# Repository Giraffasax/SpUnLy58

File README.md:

# The SpUnLy58 Keyboard
The SpUnLy58 is **Sp**layed **Un**ibody Li**ly58** layout [6*4 + 4key] keyboard. This is a minimal design keyboard that is wireless first. This design requires a Nice!Nano v2, supports a Nice!View,there are no LEDs, and a case is recommended to protect the up to 750mAh battery.

<p style="text-align: center;">Build of SpUnLy v1.2 <p>

## Notable Features
- Choc V1 support [Hotswap and Soldered]
- "Split" unibody design with 19 deg angle (measured at middle finger column)
- Column Stagger
- Aggressive Pinky splay with Minimal splay for all other columns
- Aggressive Pinky stagger
- Fanned Thumb Cluster
- Nice!Nano v2 **[ REQUIRED ]**
- Nice!View Support
- JST Battery Connector

## SpUnLy58 v1.1 Updates
- Reduced vertical spacing from 18mm -> 17mm
- Increased battery cutout from 36x52mm -> 37x57mm
- Fixed incorrect JST connector footprint
## SpUnLy58 v1.2 Updates
- Removed inner and outer column splay
- Increased pinky stagger
- Reduced thumb key spacing and increased fan angle
- Added Ground fill

### Sponsor:
PCBway sponsored the manufacturing of v1.2 main pcb and the stainless steel bottom plates. If you would like to see more pictures and read my review see them [here.](Reference/PCBWay_Review.md)
___

<p style="text-align: center;">SpUnLy58 v1 PCB<p>

<p style="text-align: center;">SpUnLy58 v1.1 PCB<p>

<p style="text-align: center;">SpUnLy58 v1.2 PCB<p>

___
## Parts List 
| Name | Quantity | Example URL |
|------|----------|-------------|
| SpUnLy58 PCB | 1  | https://github.com/Giraffasax/SpUnLy58/blob/main/KiCad/Gerber/SpUnLy58_Gerber.zip |
| Kailh Choc v1 Switches | 58 | https://typeractive.xyz/products/choc-switches?variant=46024772387047 |
| Kailh Choc v1 Keycaps (Choc Spacing) | 58 | https://fkcaps.com/custom/create/keycaps?option=mbk-pbt-pu&color=black |
| Nice!Nano v2 | 1 | https://typeractive.xyz/products/nice-nano |
| Nice!View or OLED (Optional) | 1 | https://typeractive.xyz/products/nice-view |
| Mill Max Ultra Low Profile Sockets (Optional) | 2 | https://www.littlekeyboards.com/collections/miscellaneous/products/ultra-low-profile-sockets |
| 1N4148W Diodes (SMD or TH) | 58 | https://typeractive.xyz/products/smd-diodes |
| Kailch Choc Hotswap Sockets (Optional) | 58 | https://typeractive.xyz/products/hotswap-sockets?variant=45742200324327 |
| Panasonic EVQPU Reset Switch | 1 | https://typeractive.xyz/products/reset-button |
| Alps miniature SPDT switch | 1 | https://typeractive.xyz/products/power-switch |
| JST PH 2.0mm Battery Jack | 1 | https://typeractive.xyz/products/battery-jack |
| 3.7v 750mAh 403450 Battery | 1 | https://typeractive.xyz/products/lithium-battery-750mah |

Note: I used the ultra low profile Mill Max sockets for both the controller and display to have them sit lower than the switch height to protect them in travel.

## Sandwich Case Part List
| Name | Quantity | Example URL |
|------|----------|-------------|
| Bottom Plate - PCB | 0 or 1 | https://github.com/Giraffasax/SpUnLy58/blob/main/KiCad/Gerber/Bottom_Plate_Gerber.zip |
| Bottom Plate - Metal | 0 or 1 | https://github.com/Giraffasax/SpUnLy58/blob/main/KiCad/SpUnLy58_Bottom.step |
| Top Plate | 1 | https://github.com/Giraffasax/SpUnLy58/blob/main/KiCad/Gerber/Top_Plate_Gerber.zip |
| 6mm M2 Standoffs | 10 | https://splitkb.com/products/brass-m2-spacers?variant=42396969140483 |
| 4mm M2 Screws | 20 | https://splitkb.com/products/m2-screws?_pos=2&_sid=9c9502b8a&_ss=r |

## Firmware
ZMK Firmware: https://github.com/Giraffasax/zmk-SpUnLy58-config

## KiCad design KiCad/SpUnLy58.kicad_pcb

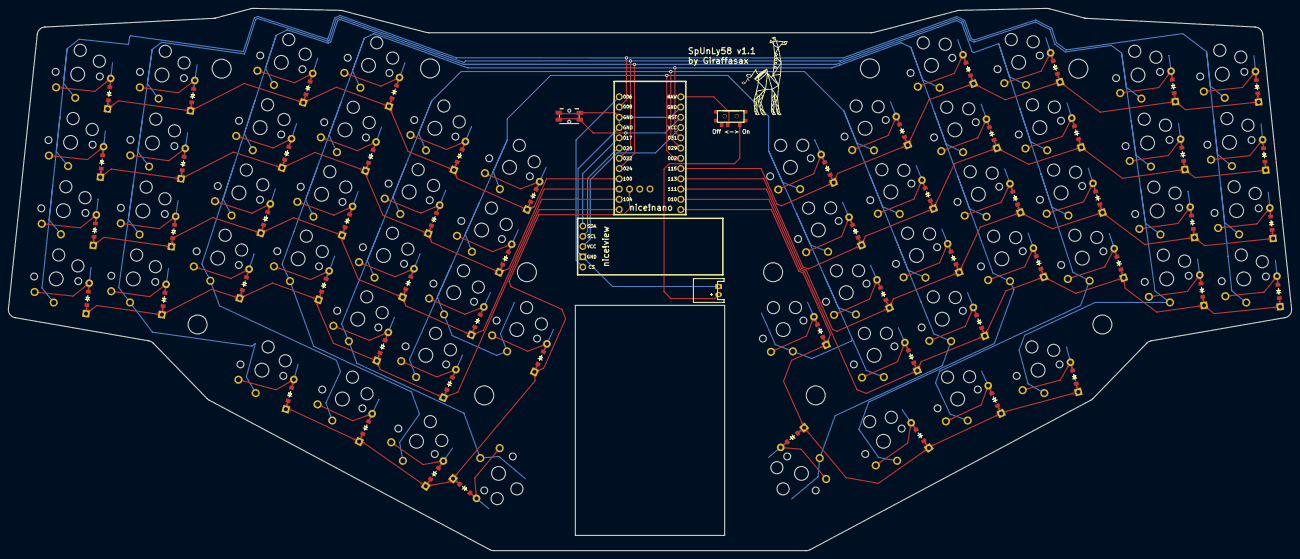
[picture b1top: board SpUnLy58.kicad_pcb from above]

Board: 2 copper layers, 318.0 x 134.4 mm, 131 parts (0 on the bottom side), 82 nets.

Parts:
B1: Panasonic_EVQPUL_EVQPUC
D1, D2, D3, D4, D5, D6, D7, D8, D9, D10, D11, D12, D13, D14, D15, D16, D17, D18, D19, D20, D21, D22, D23, D24, D25, D26, D27, D28, D29, D30, D31, D32, D33, D34, D35, D36, D37, D38, D39, D40, D41, D42, D43, D44, D45, D46, D47, D48, D49, D50, D51, D52, D53, D54, D55, D56, D57, D58: ComboDiode
JST1: JST_PH_S2B-PH-K_02x2.00mm_Angled
MCU1: nice_nano
S1, S2, S3, S4, S5, S6, S7, S8, S9, S10, S11, S12, S13, S14, S15, S16, S17, S18, S19, S20, S21, S22, S23, S24, S25, S26, S27, S28, S29, S30, S31, S32, S33, S34, S35, S36, S37, S38, S39, S40, S41, S42, S43, S44, S45, S46, S47, S48, S49, S50, S51, S52, S53, S54, S55, S56, S57, S58: Kailh_socket_PG1350_optional_mkultra
T1: SPDT_C128955
_1, _2, _3, _4, _5, _6, _7, _8, _9, _10: HOLE_M2_TH
niceView1: niceView; niceView_headers

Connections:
GND: B1.1, JST1.1, MCU1.3, MCU1.4, MCU1.23, niceView1.2
P002: MCU1.18, S21.1, S22.1, S23.1, S24.1, S25.1, S50.1, S51.1, S52.1, S53.1, S54.1
P006: MCU1.1, niceView1.1
P008: MCU1.2, S1.1, S2.1, S3.1, S4.1, S30.1, S31.1, S32.1, S33.1
P009: D54.1, D55.1, D56.1, D57.1, D58.1, MCU1.13
P010: D30.1, D34.1, D38.1, D42.1, D46.1, D50.1, MCU1.14
P011: D3.1, D7.1, D11.1, D15.1, D19.1, D23.1, MCU1.10
P017: MCU1.5, niceView1.5
P020: MCU1.6, niceView1.4
P022: MCU1.7, S5.1, S6.1, S7.1, S8.1, S26.1, S34.1, S35.1, S36.1, S37.1, S55.1
P024: MCU1.8, S9.1, S10.1, S11.1, S12.1, S27.1, S38.1, S39.1, S40.1, S41.1, S56.1
P029: MCU1.19, S17.1, S18.1, S19.1, S20.1, S29.1, S46.1, S47.1, S48.1, S49.1, S58.1
P031: MCU1.20, S13.1, S14.1, S15.1, S16.1, S28.1, S42.1, S43.1, S44.1, S45.1, S57.1
P100: D4.1, D8.1, D12.1, D16.1, D20.1, D24.1, MCU1.9
P101: D25.1, D26.1, D27.1, D28.1, D29.1, MCU1.31
P104: D2.1, D6.1, D10.1, D14.1, D18.1, D22.1, MCU1.11
P106: D1.1, D5.1, D9.1, D13.1, D17.1, D21.1, MCU1.12
P111: D31.1, D35.1, D39.1, D43.1, D47.1, D51.1, MCU1.15
P113: D32.1, D36.1, D40.1, D44.1, D48.1, D52.1, MCU1.16
P115: D33.1, D37.1, D41.1, D45.1, D49.1, D53.1, MCU1.17
RAW: MCU1.24, T1.2
RST: B1.2, MCU1.22
VCC: MCU1.21, niceView1.3
center_home: D25.2, S25.2
index_bottom: D17.2, S17.2
index_home: D18.2, S18.2
index_num: D20.2, S20.2
index_top: D19.2, S19.2
inner_bottom: D21.2, S21.2
inner_home: D22.2, S22.2
inner_num: D24.2, S24.2
inner_top: D23.2, S23.2
layer_thumb: D28.2, S28.2
main_thumb: D29.2, S29.2
middle_bottom: D13.2, S13.2
middle_home: D14.2, S14.2
middle_num: D16.2, S16.2
middle_thumb: D27.2, S27.2
middle_top: D15.2, S15.2
mirror_center_home: D54.2, S54.2
mirror_index_bottom: D46.2, S46.2
mirror_index_home: D47.2, S47.2
mirror_index_num: D49.2, S49.2
mirror_index_top: D48.2, S48.2
mirror_inner_bottom: D50.2, S50.2
mirror_inner_home: D51.2, S51.2
mirror_inner_num: D53.2, S53.2
mirror_inner_top: D52.2, S52.2
mirror_layer_thumb: D57.2, S57.2
mirror_main_thumb: D58.2, S58.2
mirror_middle_bottom: D42.2, S42.2
mirror_middle_home: D43.2, S43.2
mirror_middle_num: D45.2, S45.2
mirror_middle_thumb: D56.2, S56.2
mirror_middle_top: D44.2, S44.2
mirror_outerp_bottom: D30.2, S30.2
mirror_outerp_home: D31.2, S31.2
mirror_outerp_num: D33.2, S33.2
mirror_outerp_top: D32.2, S32.2
mirror_outerth_thumb: D55.2, S55.2
mirror_pinky_bottom: D34.2, S34.2
mirror_pinky_home: D35.2, S35.2
mirror_pinky_num: D37.2, S37.2
mirror_pinky_top: D36.2, S36.2
mirror_ring_bottom: D38.2, S38.2
mirror_ring_home: D39.2, S39.2
mirror_ring_num: D41.2, S41.2
mirror_ring_top: D40.2, S40.2
outerp_bottom: D1.2, S1.2
outerp_home: D2.2, S2.2
outerp_num: D4.2, S4.2
outerp_top: D3.2, S3.2
outerth_thumb: D26.2, S26.2
pinky_bottom: D5.2, S5.2
pinky_home: D6.2, S6.2
pinky_num: D8.2, S8.2
pinky_top: D7.2, S7.2
pos: JST1.2, T1.1
ring_bottom: D9.2, S9.2
ring_home: D10.2, S10.2
ring_num: D12.2, S12.2
ring_top: D11.2, S11.2

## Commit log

2023-06-06 Initial commit of files
2023-06-09 Added plate and bottom case pcbs Finished mounting hole positions Added new choc js file with hot swap and through hole Moved diodes
2023-06-12 Initial KiCad PCB files for keyboard and case
2023-06-12 fixed error in column net pointing to wrong pin.
2023-06-14 tuned tracks, moved mounting hole.
2023-06-17 Version 1.0 complete. Finalized routes. Added graphics.
2023-06-18 Modified plate cutout from 13.8 to 14mm
2023-07-20 Added content to README
2023-07-26 [v1.1] Reduced vertical spacing from 18 to 17mm Fixed jstph connector footprint and pad label. Increased cutout for battery.
2023-08-12 Remove stagger for outer pinky and inner columns. Tightened lateral spacing overall. Higher overall rotation of thumbkey Increased distance between halves Decrease hand angle from 20 to 17 deg
2023-08-20 Final v1p2 layout. Update yaml, kicad pcb, and gerber
2023-10-14 Final Tuning and update to README
2023-10-18 Fixed ReadME typo. Added PCBWay review. Modified pic aspect ratios.
